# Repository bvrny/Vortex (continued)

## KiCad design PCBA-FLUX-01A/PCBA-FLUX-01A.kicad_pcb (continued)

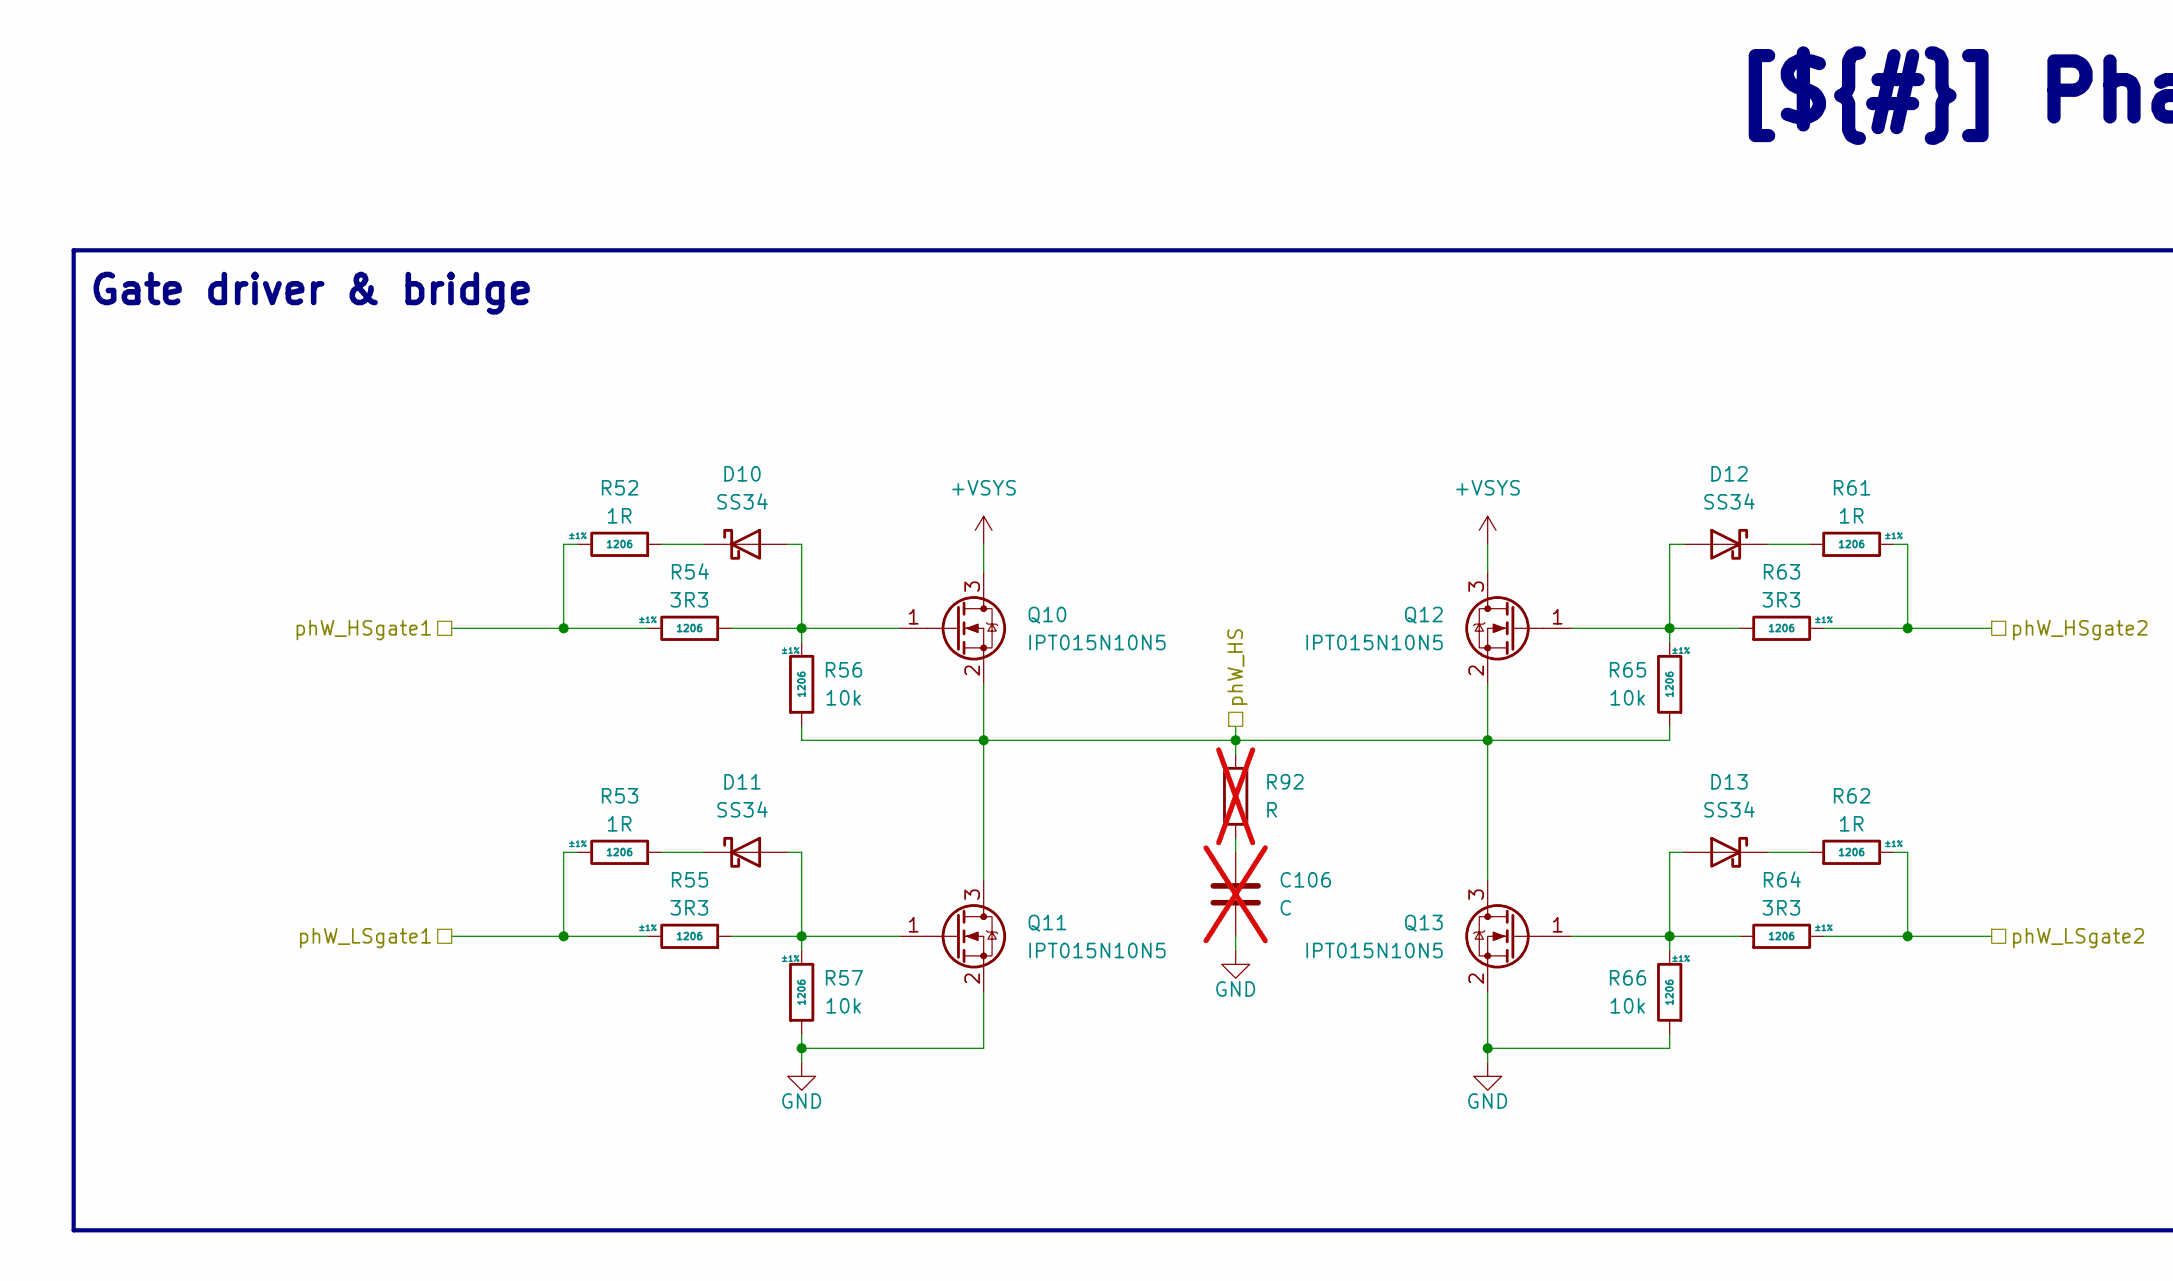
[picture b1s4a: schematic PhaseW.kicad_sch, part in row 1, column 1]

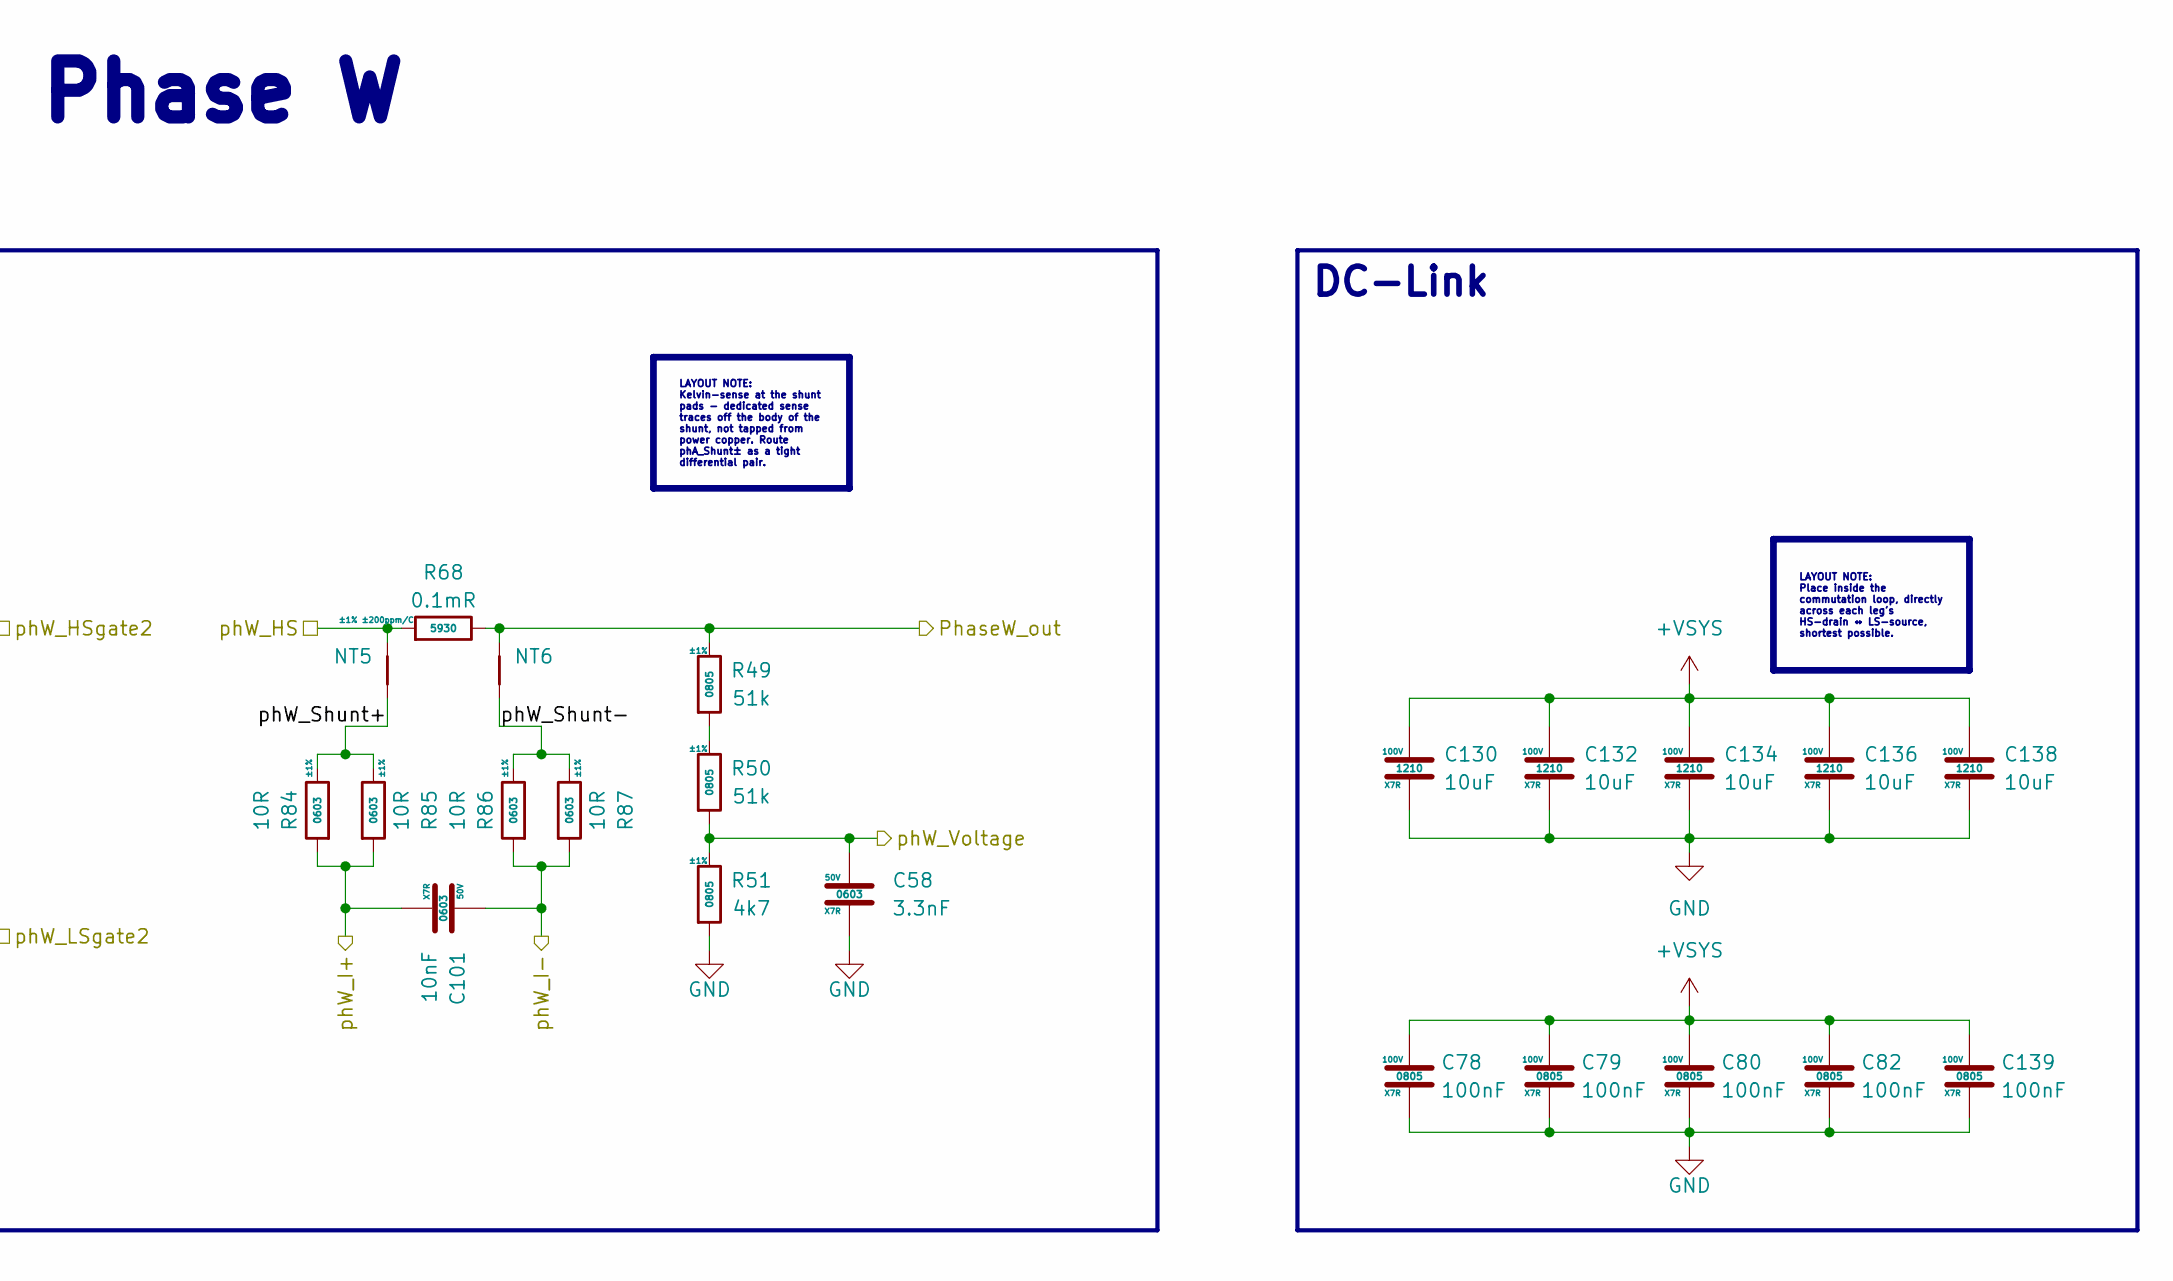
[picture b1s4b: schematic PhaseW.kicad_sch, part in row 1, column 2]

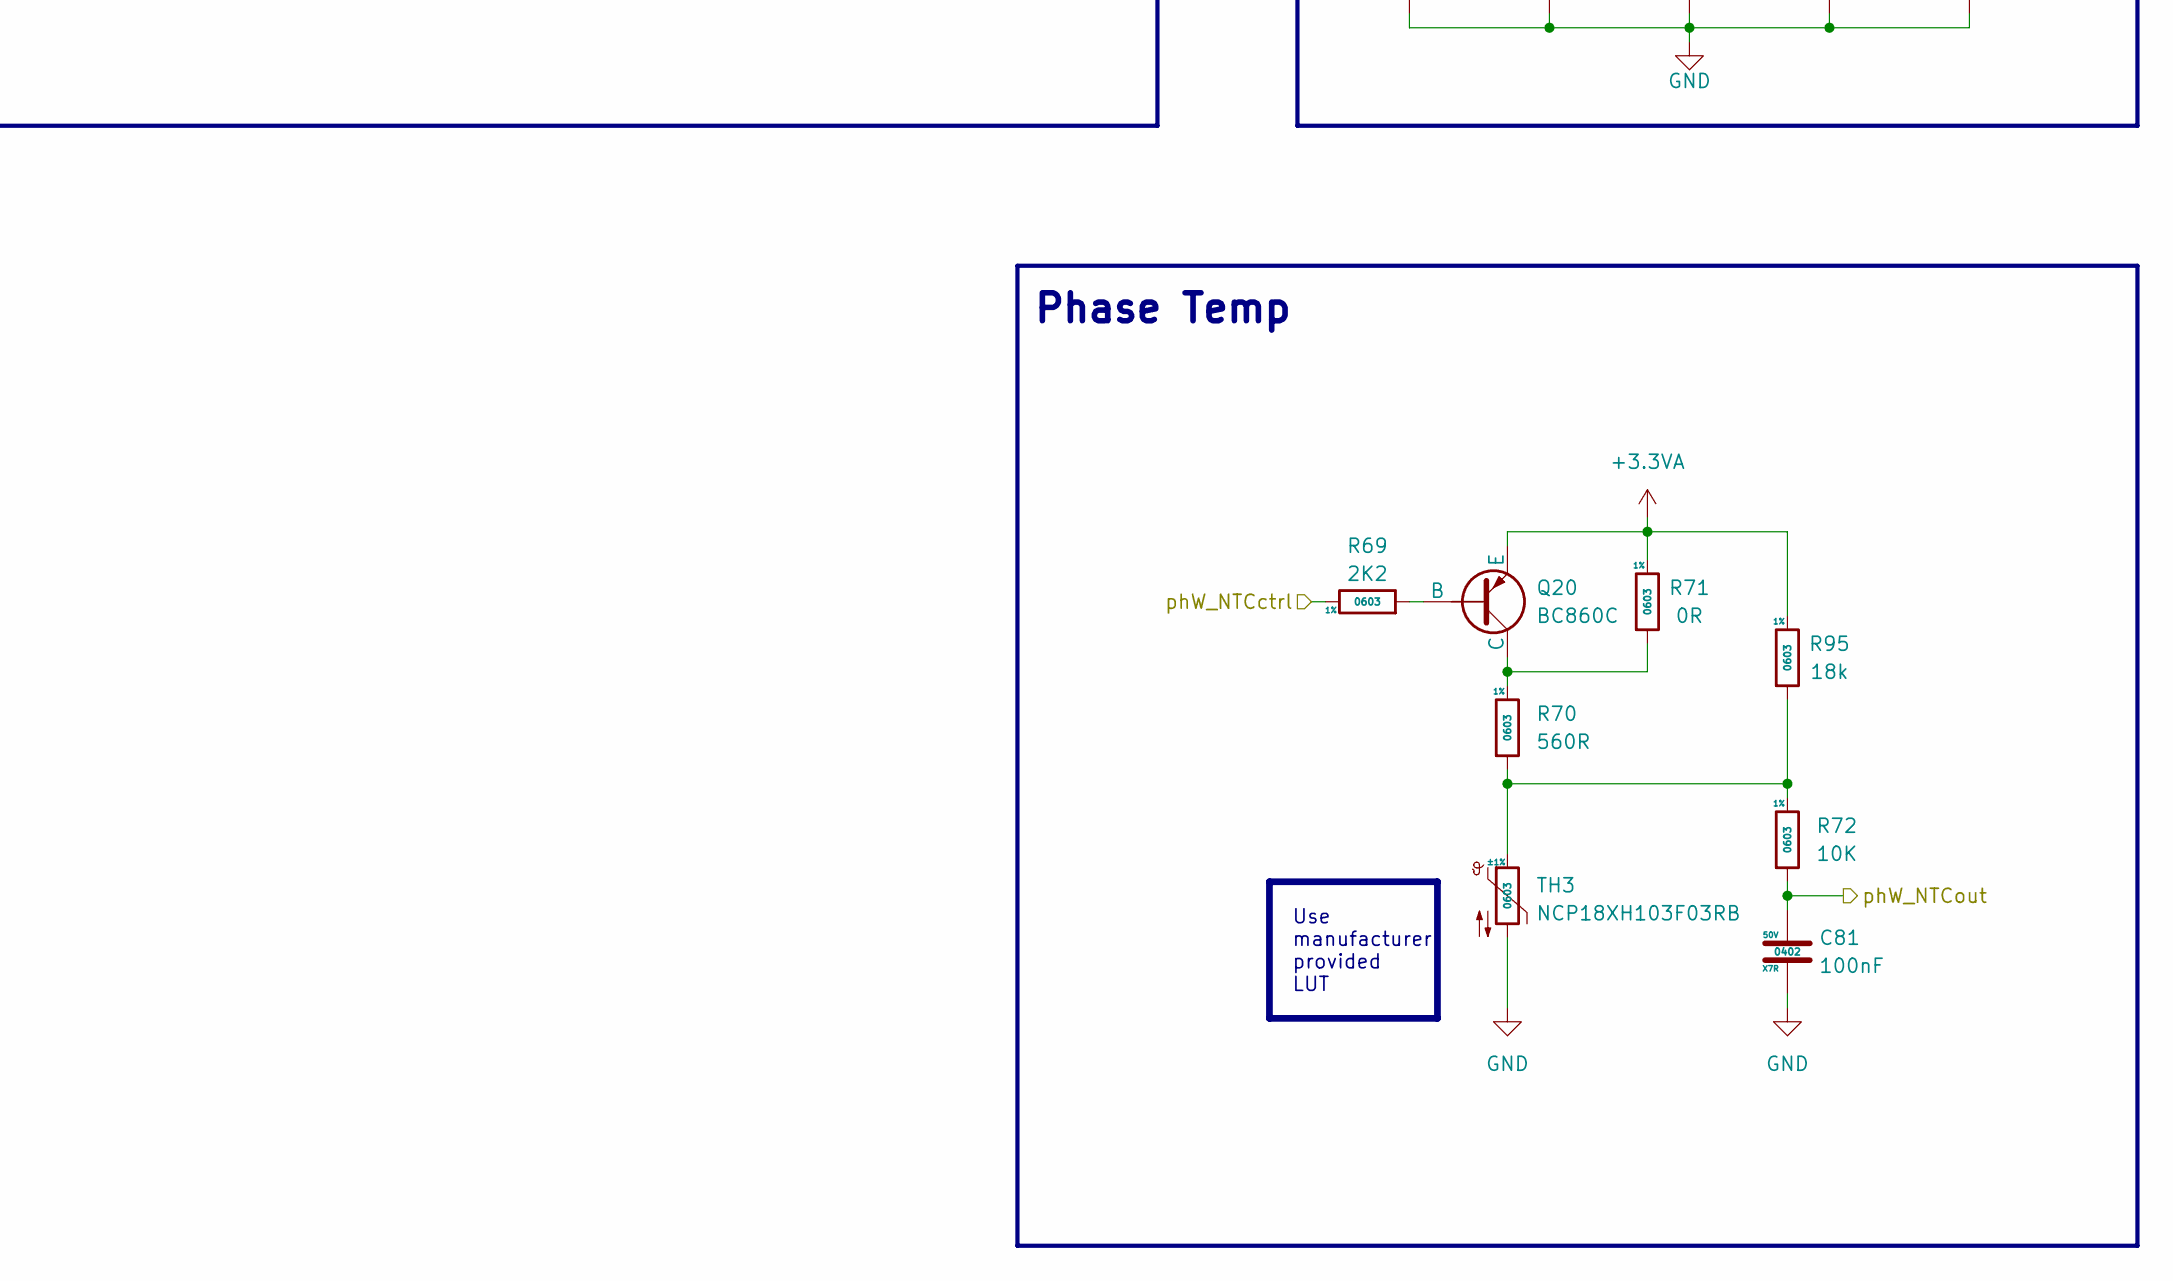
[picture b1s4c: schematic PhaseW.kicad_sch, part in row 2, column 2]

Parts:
C58: 3.3nF; C_0603_1608Metric; Voltage 50V; MFR.Part # CL10B332KB8NNNC; JLCPCB Part # C1613
C78, C79, C80, C82, C139: 100nF; C_0805_2012Metric; Voltage 100V; MFR.Part # CL21B104KCFNNNE; JLCPCB Part # C28233
C81: 100nF; C_0402_1005Metric; Voltage rating 50V; MFR.Part # CL05B104KB54PNC; JLCPCB Part # C307331
C101: 10nF; C_0603_1608Metric; Voltage 50V; MFR.Part # 0603B103K500NT; JLCPCB Part # C57112
C106: C; C_Rect_L9.0mm_W6.4mm_P7.50mm_MKT; not fitted
C130, C132, C134, C136, C138: 10uF; C_1210_3225Metric; Voltage 100V; MFR.Part # FS32X106K101EGG; JLCPCB Part # C5156756
D10, D11, D12, D13: SS34; D_SMA; JLCPCB Part # C8678
NT5, NT6: NetTie_2; NetTie-2_SMD_Pad0.5mm
Q10, Q11, Q12, Q13: IPT015N10N5; Infineon_PG-HSOF-8-1_ThermalVias; JLCPCB Part # C108964
Q20: BC860C; SOT-23; JLCPCB Part # C49309303
R49, R50: 51k; R_0805_2012Metric; Tolerance ±1%; MFR.Part # 0805W8F5102T5E; JLCPCB Part # C17737
R51: 4k7; R_0805_2012Metric; Tolerance ±1%; MFR.Part # 0805W8F4701T5E; JLCPCB Part # C17673
R52, R53, R61, R62: 1R; R_1206_3216Metric; Tolerance ±1%; MFR.Part # 1206W4F100KT5E; JLCPCB Part # C17928
R54, R55, R63, R64: 3R3; R_1206_3216Metric; Tolerance ±1%; MFR.Part # NS06W4F330KT5E; JLCPCB Part # C2783335
R56, R57, R65, R66: 10k; R_1206_3216Metric; Tolerance ±1%; MFR.Part # 1206W4F1002T5E; JLCPCB Part # C17902
R68: 0.1mR; R5930; Tolerance ±1% ±200ppm/C; MFR.Part # ASR-S-7-0.1F; JLCPCB Part # C6075508
R69: 2K2; R_0603_1608Metric; Tolerance 1%; MFR.Part # 0603WAF2201T5E; JLCPCB Part # C4190
R70: 560R; R_0603_1608Metric; Tolerance 1%; MFR.Part # 0603WAF5600T5E; JLCPCB Part # C23204
R71: 0R; R_0603_1608Metric; Tolerance 1%; MFR.Part # 0603WAF0000T5E; JLCPCB Part # C21189
R72: 10K; R_0603_1608Metric; Tolerance 1%; MFR.Part # 0603WAF1002T5E; JLCPCB Part # C25804
R84, R85, R86, R87: 10R; R_0805_2012Metric; Tolerance ±1%; MFR.Part # 0603WAF100JT5E; JLCPCB Part # C22859
R92: R; R_1218_3246Metric; not fitted
R95: 18k; R_0603_1608Metric; Tolerance 1%; MFR.Part # 0603WAF1802T5E; JLCPCB Part # C25810
TH3: NCP18XH103F03RB; R_0603_1608Metric; Tolerance ±1%; JLCPCB Part # C13564

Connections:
+3.3VA: Q20.3 (E), R71.1, R95.1; also elsewhere on the board
+VSYS: C78.1, C79.1, C80.1, C82.1, C130.1, C132.1, C134.1, C136.1, C138.1, C139.1, Q10.3, Q12.3; also elsewhere on the board
/Project Architecture/Phase W/PhaseW_out: NT6.2, R49.1, R68.1; also elsewhere on the board
/Project Architecture/Phase W/phW_HS: NT5.2, Q10.2, Q11.3, Q12.2, Q13.3, R56.2, R65.2, R68.2, R92.1; also elsewhere on the board
/Project Architecture/Phase W/phW_HSgate1: R52.1, R54.1; also elsewhere on the board
/Project Architecture/Phase W/phW_HSgate2: R61.1, R63.1; also elsewhere on the board
/Project Architecture/Phase W/phW_I+: C101.2, R84.2, R85.2; also elsewhere on the board
/Project Architecture/Phase W/phW_I-: C101.1, R86.2, R87.2; also elsewhere on the board
/Project Architecture/Phase W/phW_LSgate1: R53.1, R55.1; also elsewhere on the board
/Project Architecture/Phase W/phW_LSgate2: R62.1, R64.1; also elsewhere on the board
/Project Architecture/Phase W/phW_NTCctrl: R69.1; also elsewhere on the board
/Project Architecture/Phase W/phW_NTCout: C81.1, R72.2; also elsewhere on the board
/Project Architecture/Phase W/phW_Shunt+: NT5.1, R84.1, R85.1
/Project Architecture/Phase W/phW_Shunt-: NT6.1, R86.1, R87.1
/Project Architecture/Phase W/phW_Voltage: C58.1, R50.2, R51.1; also elsewhere on the board
GND: C58.2, C78.2, C79.2, C80.2, C81.2, C82.2, C106.2, C130.2, C132.2, C134.2, C136.2, C138.2, C139.2, Q11.2, Q13.2, R51.2, R57.2, R66.2, TH3.2; also elsewhere on the board
unnamed: C106.1, R92.2
unnamed: D10.2 (A), Q10.1, R54.2, R56.1
unnamed: D10.1 (K), R52.2
unnamed: D11.2 (A), Q11.1, R55.2, R57.1
unnamed: D11.1 (K), R53.2
unnamed: D12.2 (A), Q12.1, R63.2, R65.1
unnamed: D12.1 (K), R61.2
unnamed: D13.2 (A), Q13.1, R64.2, R66.1
unnamed: D13.1 (K), R62.2
unnamed: Q20.2 (B), R69.2
unnamed: Q20.1 (C), R70.1, R71.2
unnamed: R49.2, R50.1
unnamed: R70.2, R72.1, R95.2, TH3.1

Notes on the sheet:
Gate driver & bridge
Phase Temp
DC-Link
LAYOUT NOTE: Kelvin-sense at the shunt pads - dedicated sense traces off the body of the shunt, not tapped from power copper. Route phA_Shunt± as a tight differential pair.
Use manufacturer provided LUT
LAYOUT NOTE: Place inside the commutation loop, directly across each leg's HS-drain ↔ LS-source, shortest possible.
[${#}] Phase W

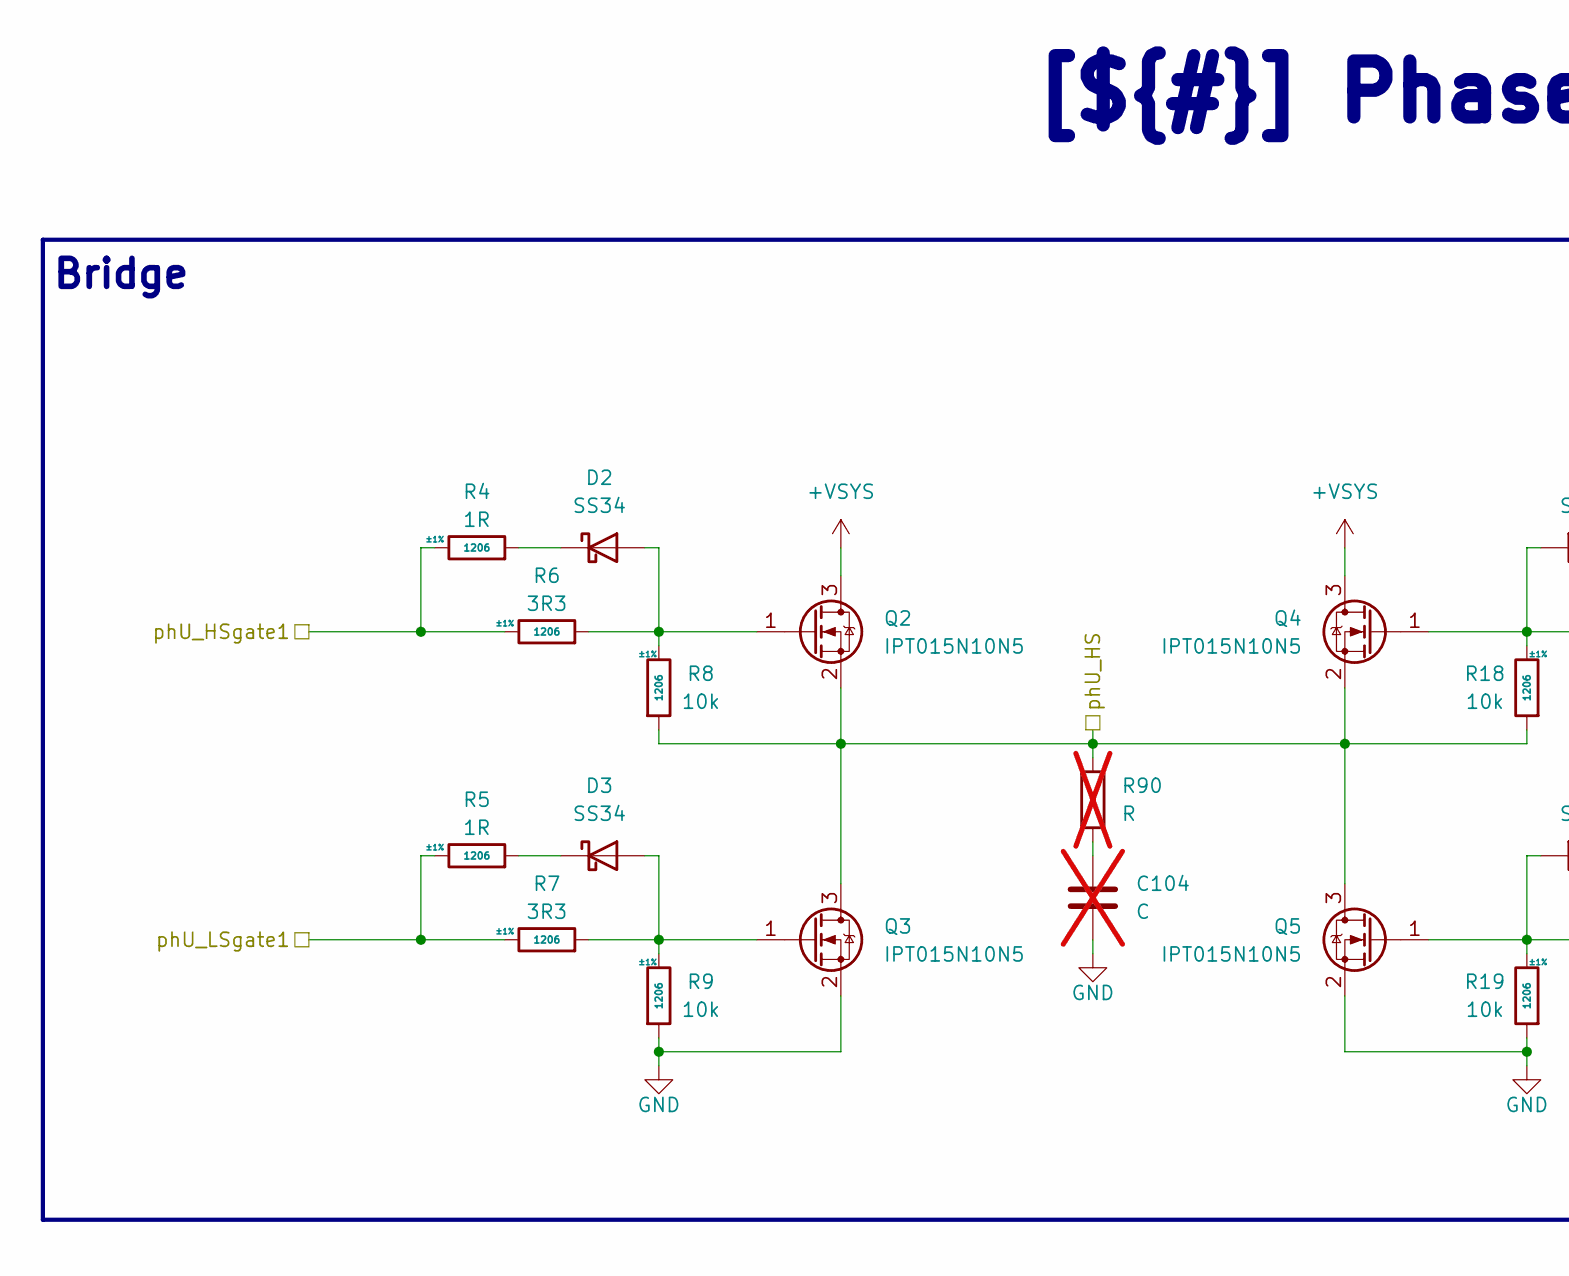
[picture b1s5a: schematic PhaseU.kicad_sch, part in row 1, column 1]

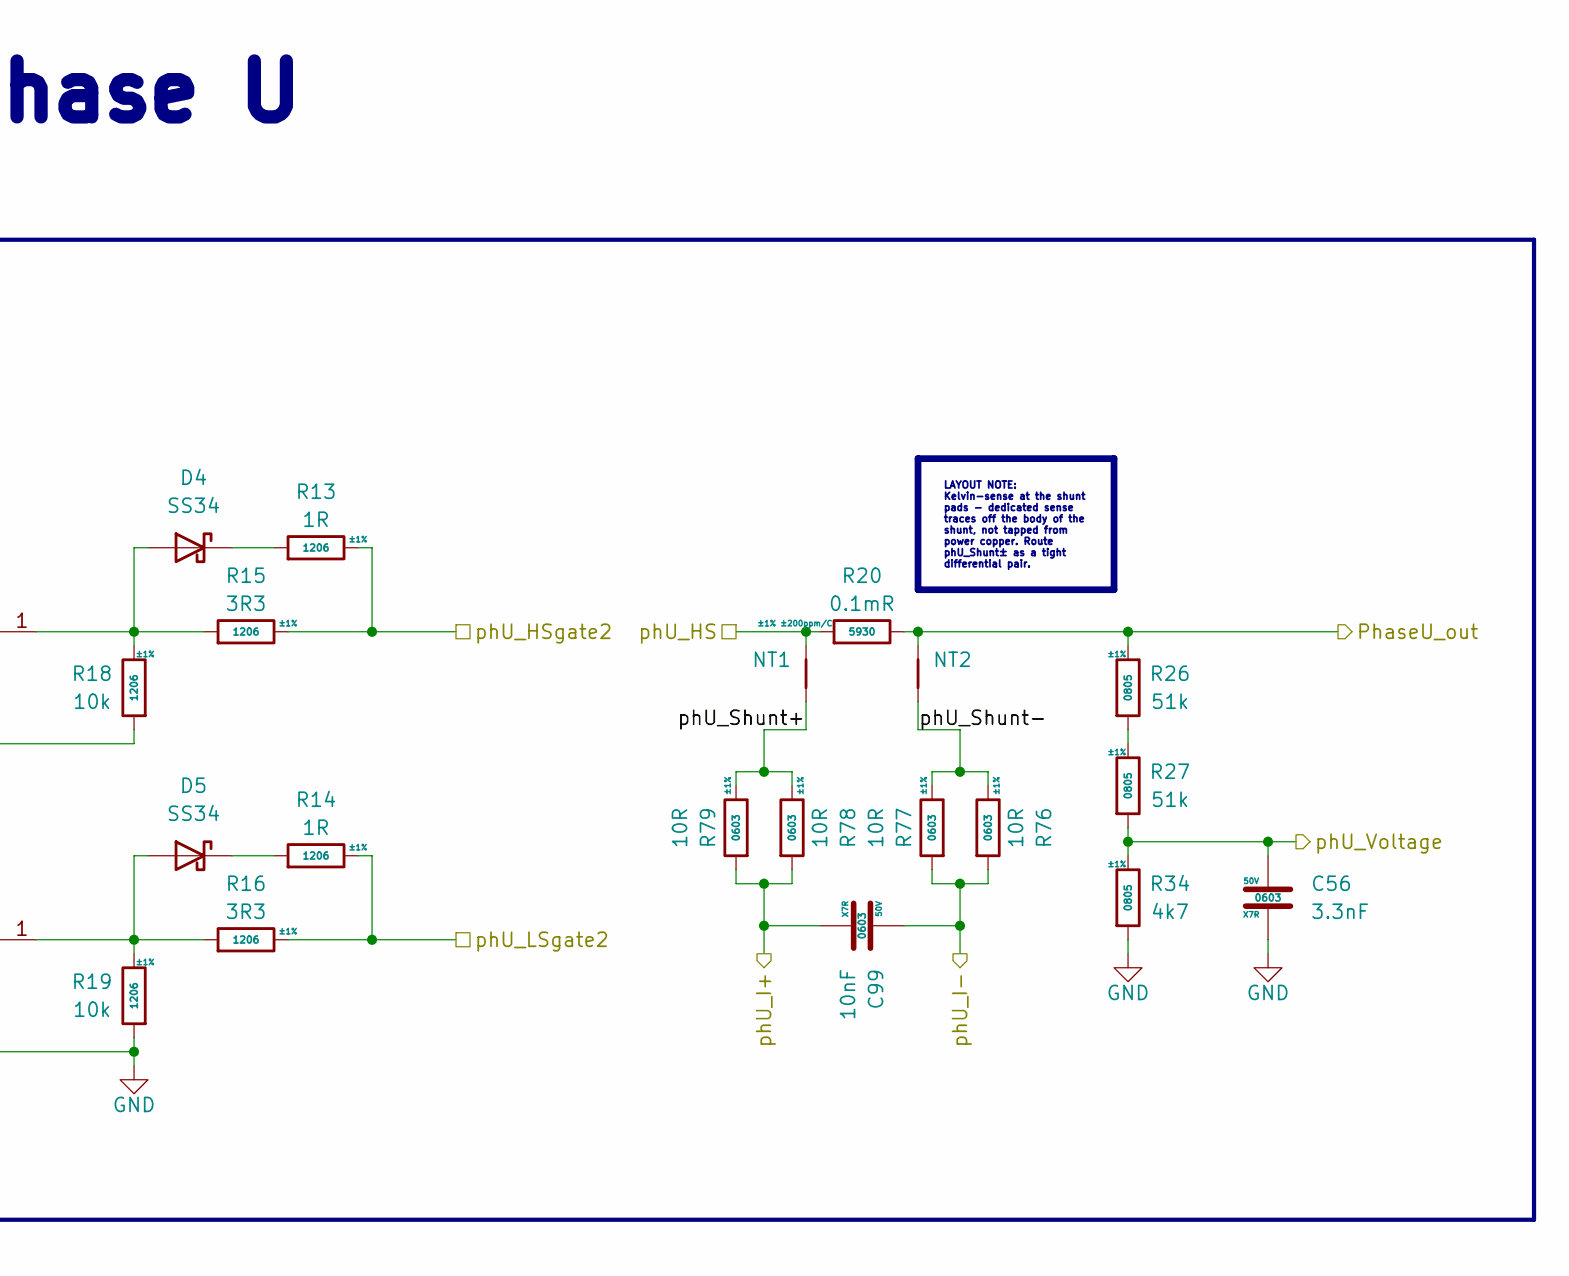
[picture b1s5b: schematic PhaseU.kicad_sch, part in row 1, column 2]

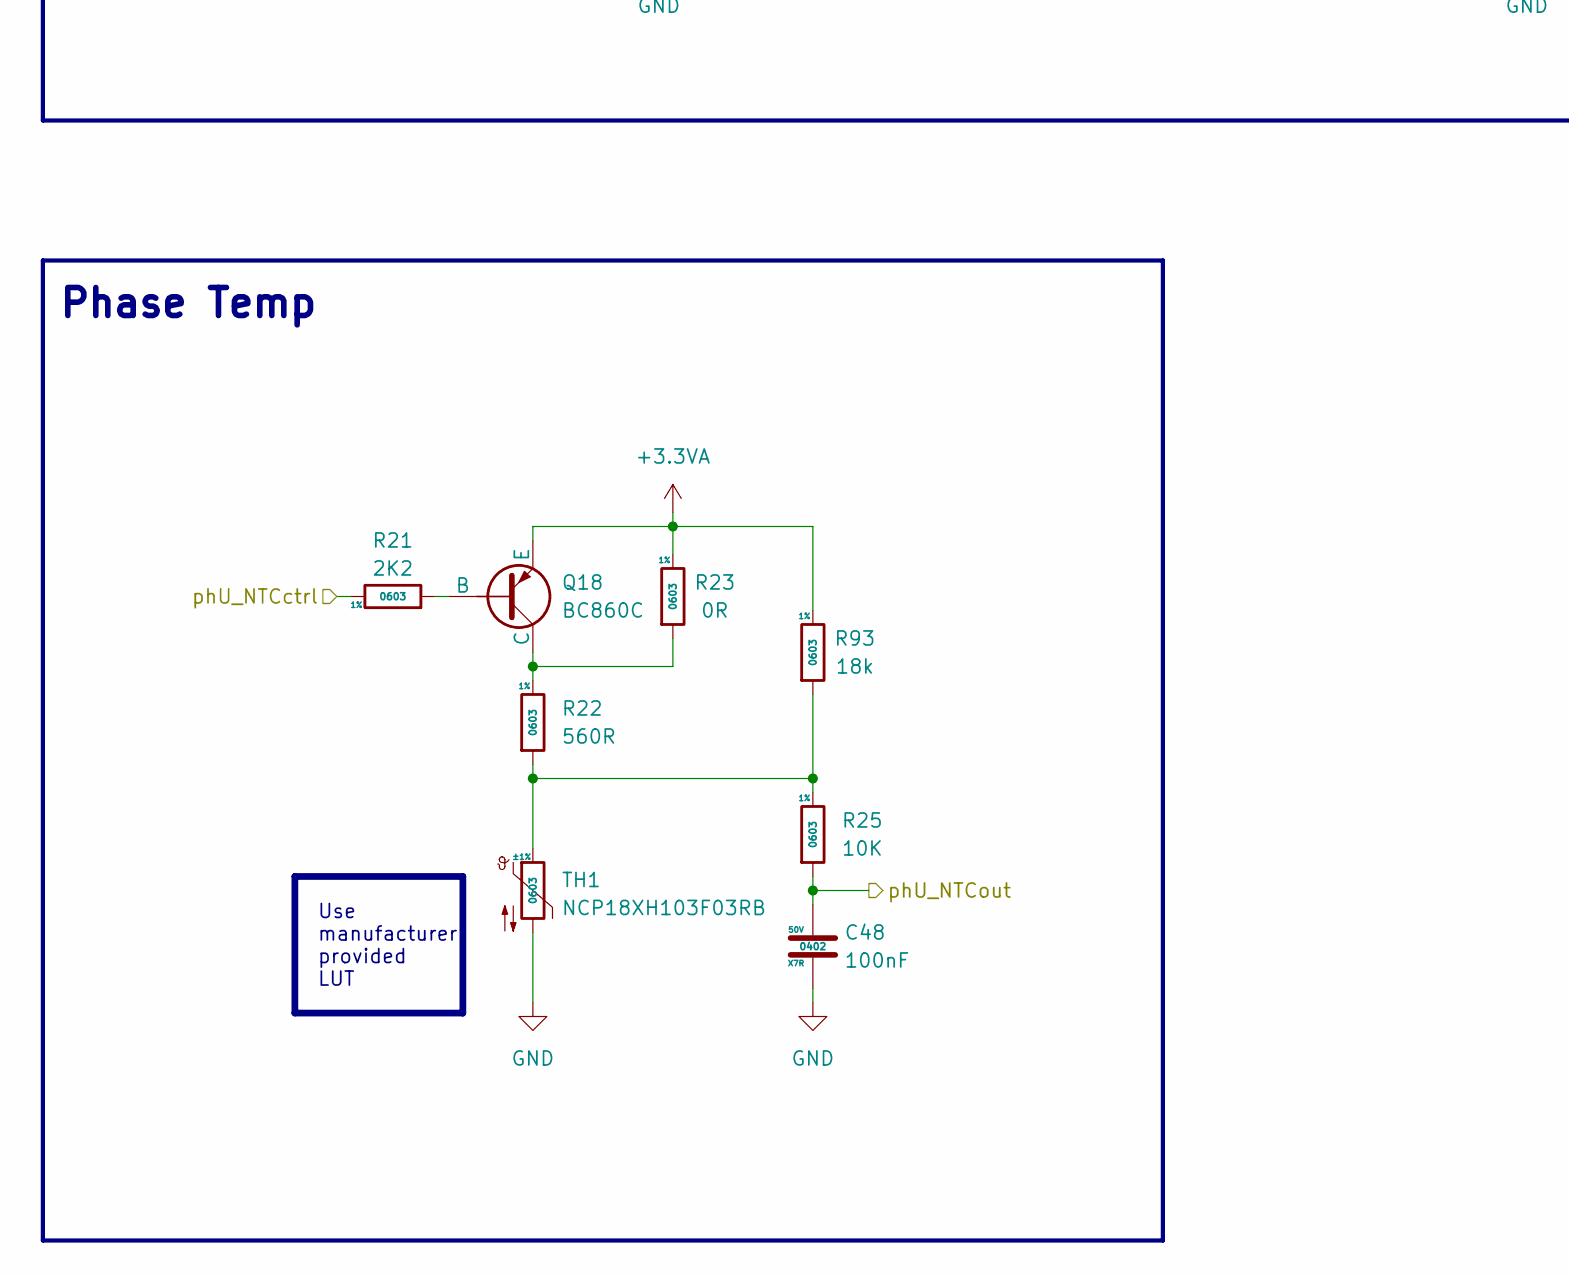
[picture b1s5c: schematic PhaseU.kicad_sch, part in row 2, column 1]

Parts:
C48: 100nF; C_0402_1005Metric; Voltage rating 50V; MFR.Part # CL05B104KB54PNC; JLCPCB Part # C307331
C56: 3.3nF; C_0603_1608Metric; Voltage 50V; MFR.Part # CL10B332KB8NNNC; JLCPCB Part # C1613
C99: 10nF; C_0603_1608Metric; Voltage 50V; MFR.Part # 0603B103K500NT; JLCPCB Part # C57112
C104: C; C_Rect_L9.0mm_W6.4mm_P7.50mm_MKT; not fitted
D2, D3, D4, D5: SS34; D_SMA; JLCPCB Part # C8678
NT1, NT2: NetTie_2; NetTie-2_SMD_Pad0.5mm
Q2, Q3, Q4, Q5: IPT015N10N5; Infineon_PG-HSOF-8-1_ThermalVias; JLCPCB Part # C108964
Q18: BC860C; SOT-23; JLCPCB Part # C49309303
R4, R5, R13, R14: 1R; R_1206_3216Metric; Tolerance ±1%; MFR.Part # 1206W4F100KT5E; JLCPCB Part # C17928
R6, R7, R15, R16: 3R3; R_1206_3216Metric; Tolerance ±1%; MFR.Part # NS06W4F330KT5E; JLCPCB Part # C2783335
R8, R9, R18, R19: 10k; R_1206_3216Metric; Tolerance ±1%; MFR.Part # 1206W4F1002T5E; JLCPCB Part # C17902
R20: 0.1mR; R5930; Tolerance ±1% ±200ppm/C; MFR.Part # ASR-S-7-0.1F; JLCPCB Part # C6075508
R21: 2K2; R_0603_1608Metric; Tolerance 1%; MFR.Part # 0603WAF2201T5E; JLCPCB Part # C4190
R22: 560R; R_0603_1608Metric; Tolerance 1%; MFR.Part # 0603WAF5600T5E; JLCPCB Part # C23204
R23: 0R; R_0603_1608Metric; Tolerance 1%; MFR.Part # 0603WAF0000T5E; JLCPCB Part # C21189
R25: 10K; R_0603_1608Metric; Tolerance 1%; MFR.Part # 0603WAF1002T5E; JLCPCB Part # C25804
R26, R27: 51k; R_0805_2012Metric; Tolerance ±1%; MFR.Part # 0805W8F5102T5E; JLCPCB Part # C17737
R34: 4k7; R_0805_2012Metric; Tolerance ±1%; MFR.Part # 0805W8F4701T5E; JLCPCB Part # C17673
R76, R77, R78, R79: 10R; R_0805_2012Metric; Tolerance ±1%; MFR.Part # 0603WAF100JT5E; JLCPCB Part # C22859
R90: R; R_1218_3246Metric; not fitted
R93: 18k; R_0603_1608Metric; Tolerance 1%; MFR.Part # 0603WAF1802T5E; JLCPCB Part # C25810
TH1: NCP18XH103F03RB; R_0603_1608Metric; Tolerance ±1%; JLCPCB Part # C13564

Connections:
+3.3VA: Q18.3 (E), R23.1, R93.1; also elsewhere on the board
+VSYS: Q2.3, Q4.3; also elsewhere on the board
/Project Architecture/Phase U/PhaseU_out: NT2.2, R20.1, R26.1; also elsewhere on the board
/Project Architecture/Phase U/phU_HS: NT1.2, Q2.2, Q3.3, Q4.2, Q5.3, R8.2, R18.2, R20.2, R90.1; also elsewhere on the board
/Project Architecture/Phase U/phU_HSgate1: R4.1, R6.1; also elsewhere on the board
/Project Architecture/Phase U/phU_HSgate2: R13.1, R15.1; also elsewhere on the board
/Project Architecture/Phase U/phU_I+: C99.2, R78.2, R79.2; also elsewhere on the board
/Project Architecture/Phase U/phU_I-: C99.1, R76.2, R77.2; also elsewhere on the board
/Project Architecture/Phase U/phU_LSgate1: R5.1, R7.1; also elsewhere on the board
/Project Architecture/Phase U/phU_LSgate2: R14.1, R16.1; also elsewhere on the board
/Project Architecture/Phase U/phU_NTCctrl: R21.1; also elsewhere on the board
/Project Architecture/Phase U/phU_NTCout: C48.1, R25.2; also elsewhere on the board
/Project Architecture/Phase U/phU_Shunt+: NT1.1, R78.1, R79.1
/Project Architecture/Phase U/phU_Shunt-: NT2.1, R76.1, R77.1
/Project Architecture/Phase U/phU_Voltage: C56.1, R27.2, R34.1; also elsewhere on the board
GND: C48.2, C56.2, C104.2, Q3.2, Q5.2, R9.2, R19.2, R34.2, TH1.2; also elsewhere on the board
unnamed: C104.1, R90.2
unnamed: D2.2 (A), Q2.1, R6.2, R8.1
unnamed: D2.1 (K), R4.2
unnamed: D3.2 (A), Q3.1, R7.2, R9.1
unnamed: D3.1 (K), R5.2
unnamed: D4.2 (A), Q4.1, R15.2, R18.1
unnamed: D4.1 (K), R13.2
unnamed: D5.2 (A), Q5.1, R16.2, R19.1
unnamed: D5.1 (K), R14.2
unnamed: Q18.2 (B), R21.2
unnamed: Q18.1 (C), R22.1, R23.2
unnamed: R22.2, R25.1, R93.2, TH1.1
unnamed: R26.2, R27.1

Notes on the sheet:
Bridge
Phase Temp
LAYOUT NOTE: Kelvin-sense at the shunt pads - dedicated sense traces off the body of the shunt, not tapped from power copper. Route phU_Shunt± as a tight differential pair.
Use manufacturer provided LUT
LAYOUT NOTE: Place inside the commutation loop, directly across each leg's HS-drain ↔ LS-source, shortest possible.
[${#}] Phase U

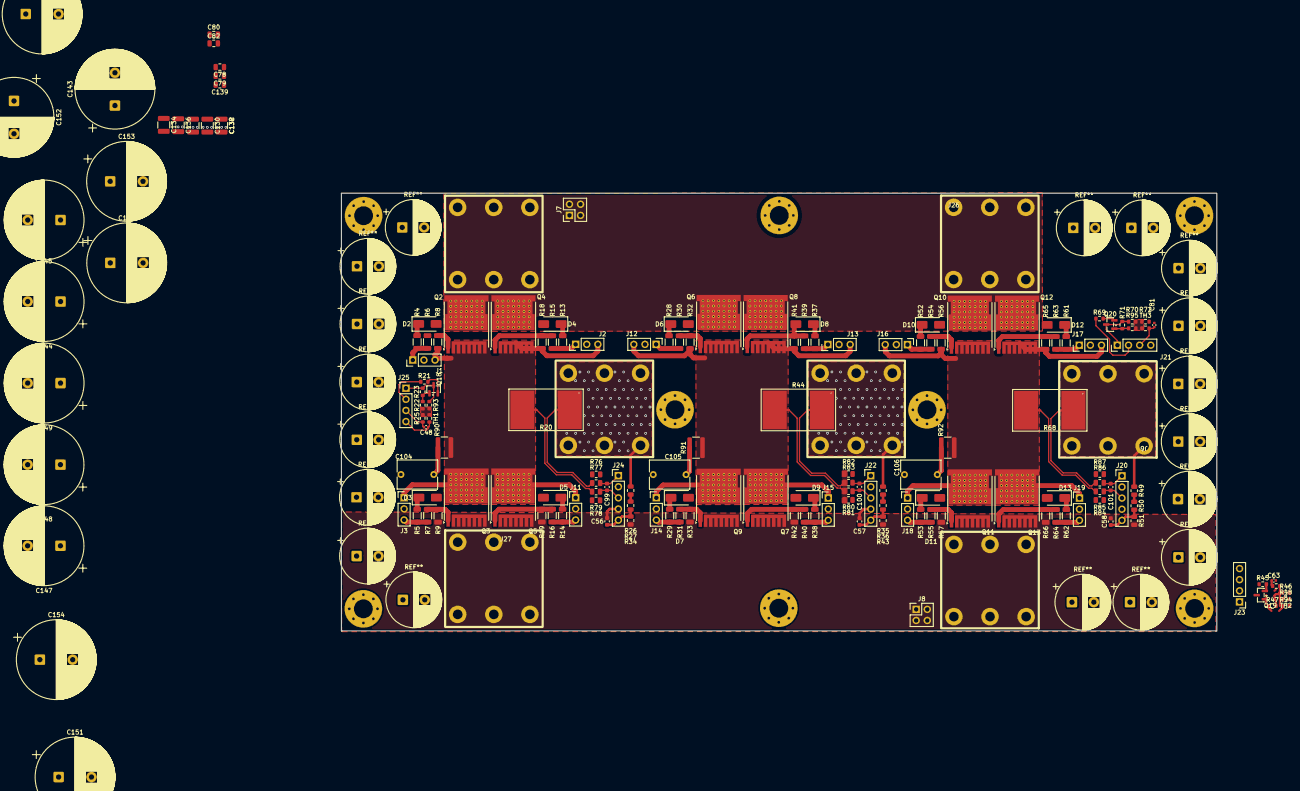
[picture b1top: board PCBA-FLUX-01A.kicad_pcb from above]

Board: 2 copper layers, 200.0 x 100.0 mm, 183 parts (0 on the bottom side), 81 nets.

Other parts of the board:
H1, H2, H3, H4, H5, H6, H7, H8: MountingHole; MountingHole_4.3mm_M4_Pad_Via
J26, J27: Screw_Terminal_01x01; M8_NutTerminal

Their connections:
+VSYS: J26.1 (Pin_1_1); also elsewhere on the board
GND: J27.1 (Pin_1_1); also elsewhere on the board

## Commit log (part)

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2026-06-22 Finished inverter design and started working on MCU pin out
